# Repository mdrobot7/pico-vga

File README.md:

# Reqirements
This code was developed on Windows 11 using the Raspberry Pi Pico official C++ SDK and Visual Studio Code. It is intended to work in that environment, and no guarantees are made that it will build cleanly with no extra configuration on Linux or MacOS. However, the compiled `.uf2` file will work regardless of the OS used.

## Software Dependencies
- Raspberry Pi Pico C++ SDK, and its dependencies (see official setup instructions)
- CMake
- Visual Studio Code
- Python 3.10+
- OpenCV-Python 4.6.0+
- Numpy

## Hardware Requirements
- A Raspberry Pi Pico, obviously!
- A monitor with VGA input
- A breadboard, or a piece of protoboard/perfboard if doing a complete assembly

Since VGA is a true analog signal, it is not enough to cut up a sacrificial cable and tie it onto the Pico's pins. Some extra hardware is required to make color work, which is why a breadboard is highly recommended.

# Configuration
You **must** clone this repository ALONGSIDE the Pi Pico SDK, otherwise it WILL NOT BUILD! The file tree must look like this:

/
- pico-sdk/
- pico-vga/

### Alternative Configuration Instructions
If you absolutely cannot clone it alongside the SDK, then edit ```CMakeLists.txt``` lines 8 and 9 to match the path to those files within the SDK.

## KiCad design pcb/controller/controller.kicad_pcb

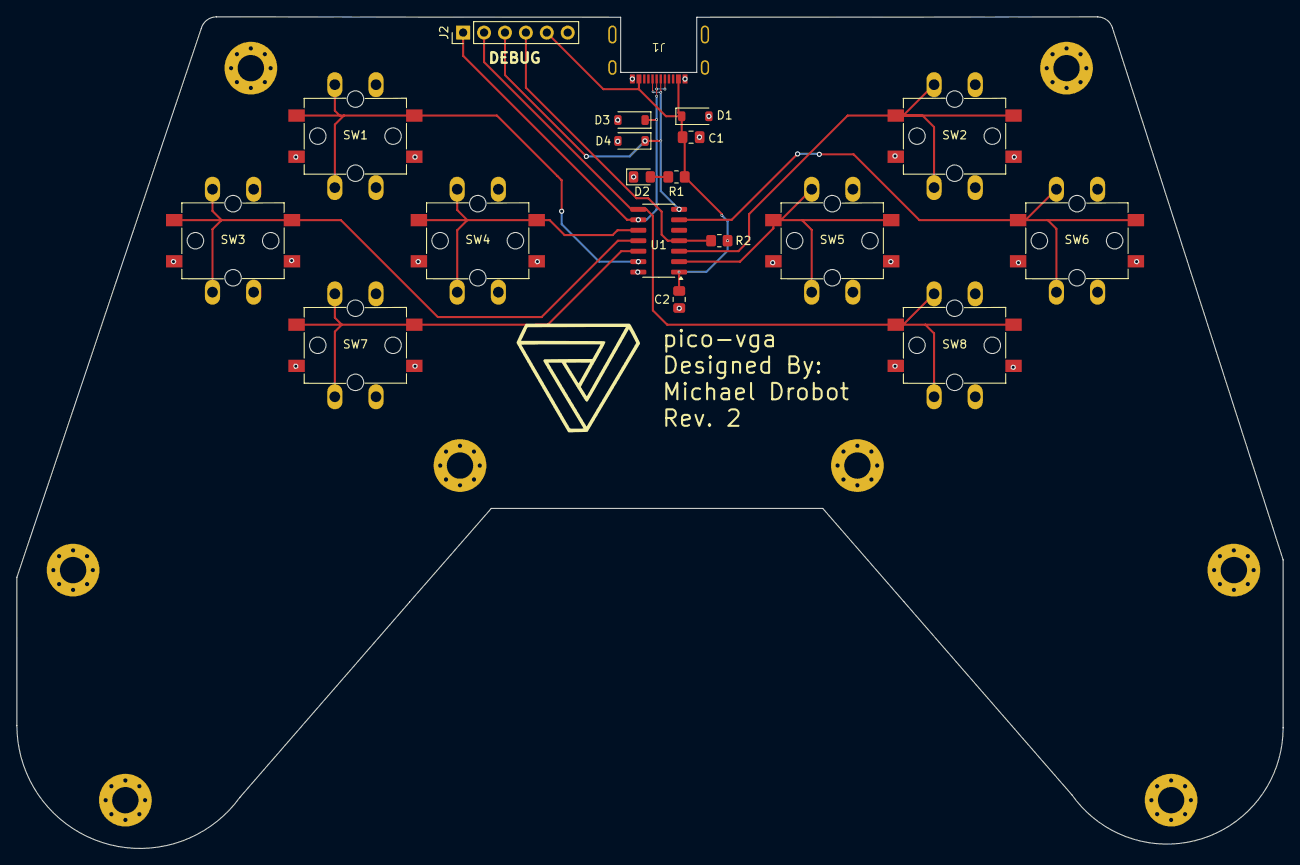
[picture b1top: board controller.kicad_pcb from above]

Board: 2 copper layers, 153.8 x 101.0 mm, 19 parts (0 on the bottom side), 14 nets.

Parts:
C1: 10u; C_0805_2012Metric_Pad1.18x1.45mm_HandSolder
C2: 100n; C_0805_2012Metric_Pad1.18x1.45mm_HandSolder
D1, D3, D4: 3.6V; D_SOD-123
D2: LED; LED_0805_2012Metric_Pad1.15x1.40mm_HandSolder
J1: USB_C_Receptacle_USB2.0_16P; USB_C_Receptacle_Molex_2169900003
J2: Conn_01x06_Pin; PinHeader_1x06_P2.54mm_Vertical
R1: 4.7K; R_0805_2012Metric_Pad1.20x1.40mm_HandSolder
R2: 4.7k; R_0805_2012Metric_Pad1.20x1.40mm_HandSolder
SW1, SW2, SW3, SW4, SW5, SW6, SW7, SW8: SW_Push; SW_Push_1P1T_12MM_SMD_AND_THT
U1: ATtiny24A-SS; SOIC-14_3.9x8.7mm_P1.27mm

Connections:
+3V3: C1.2, C2.1, D1.1 (K), J1.A4 (VBUS), J1.B4 (VBUS), J2.5, R1.1, R2.2, U1.1 (VCC)
/BTN_A: J2.2, SW8.1, U1.8 (PA5)
/BTN_B: SW6.1, U1.6 (PA7)
/BTN_DOWN: SW7.1, U1.12 (PA1)
/BTN_LEFT: SW3.1, U1.11 (PA2)
/BTN_RIGHT: SW4.1, U1.10 (PA3)
/BTN_UP: SW1.1, U1.13 (AREF/PA0)
/BTN_X: SW5.1, U1.2 (XTAL1/PB0)
/BTN_Y: SW2.1, U1.3 (XTAL2/PB1)
/MOSI: D4.1 (K), J1.A6 (D+), J1.B6 (D+), J2.3, U1.7 (PA6)
/RST: J2.4, R2.1, U1.4 (~RESET/PB3)
/SCK: D3.1 (K), J1.A7 (D-), J1.B7 (D-), J2.1, U1.9 (PA4)
GND: C1.1, C2.2, D1.2 (A), D2.1 (K), D3.2 (A), D4.2 (A), J1.A1 (GND), J1.B1 (GND), J1.S1 (SHIELD), J2.6, SW1.2, SW2.2, SW3.2, SW4.2, SW5.2, SW6.2, SW7.2, SW8.2, U1.14 (GND)
unnamed: D2.2 (A), R1.2

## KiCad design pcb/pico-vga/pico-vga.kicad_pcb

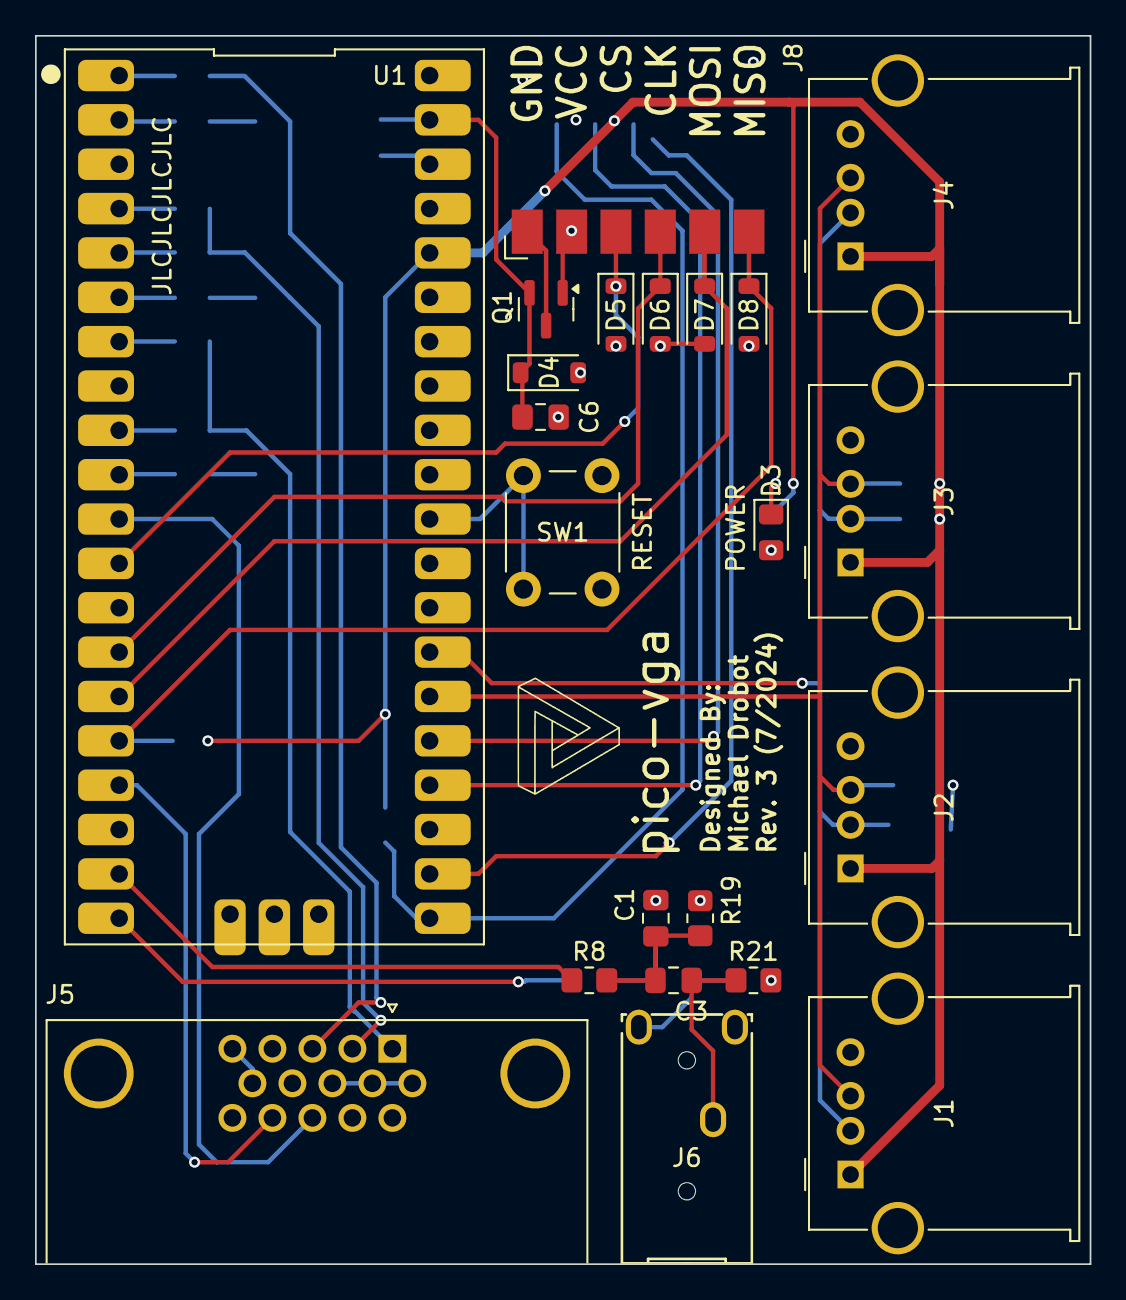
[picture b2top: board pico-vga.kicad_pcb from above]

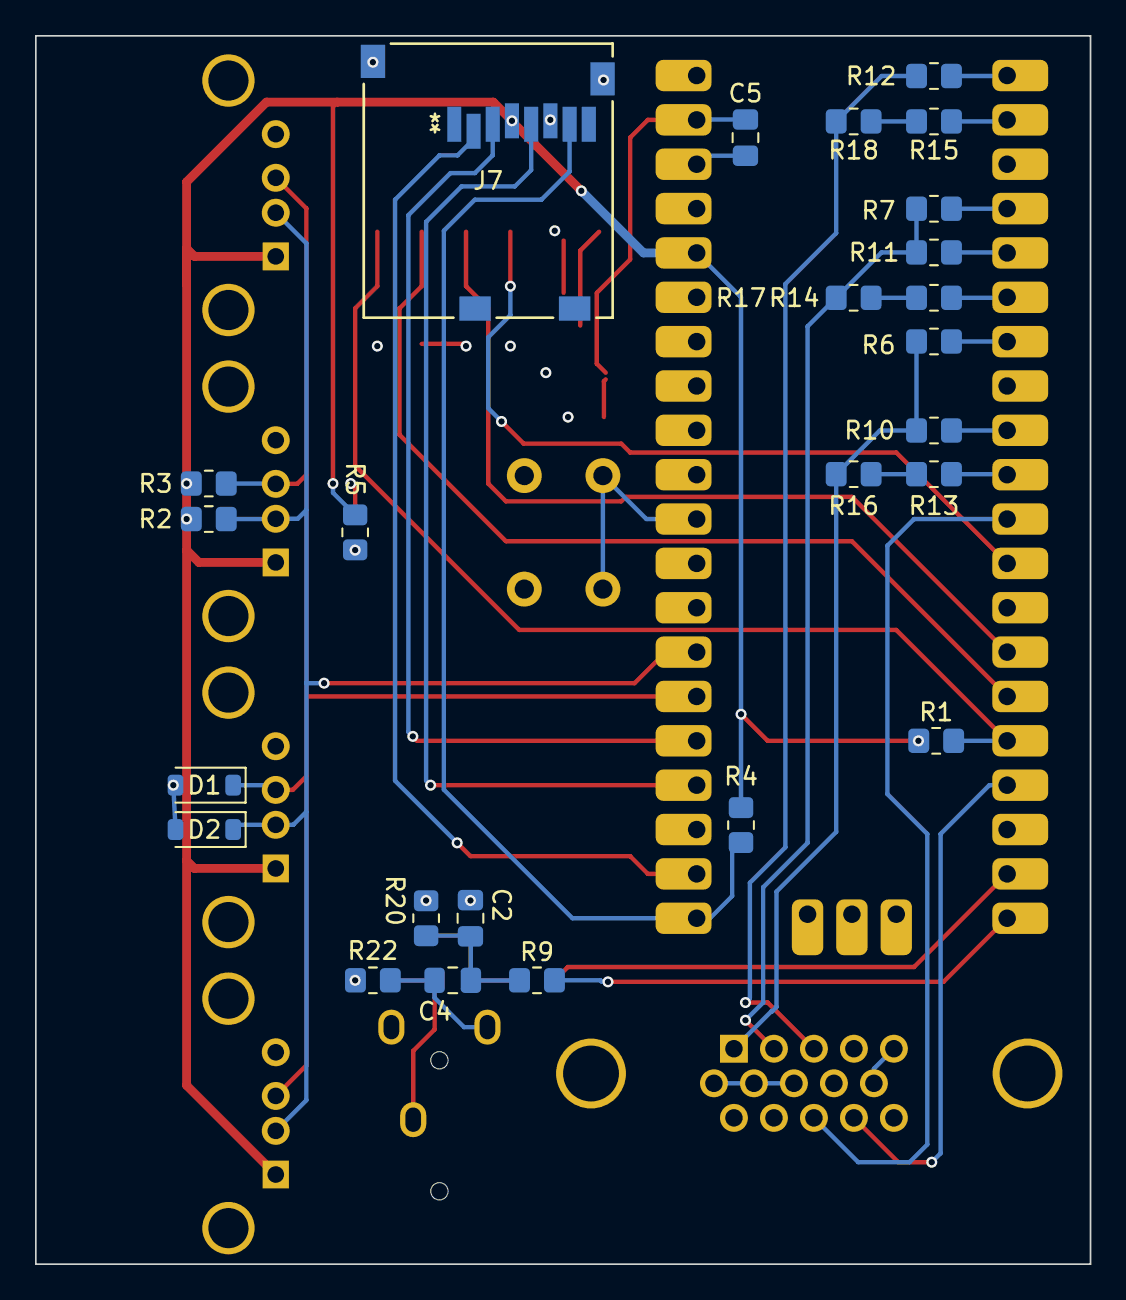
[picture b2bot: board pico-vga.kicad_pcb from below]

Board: 4 copper layers, 60.4 x 70.3 mm, 47 parts (25 on the bottom side), 38 nets.

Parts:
C1, C2, C5: 100n; C_0805_2012Metric_Pad1.18x1.45mm_HandSolder
C3, C4: 47u; C_0805_2012Metric_Pad1.18x1.45mm_HandSolder
C6: 10u; C_0805_2012Metric_Pad1.18x1.45mm_HandSolder
D1, D2, D5, D6, D7, D8: 3.6V; D_SOD-123
D3: LED; LED_0805_2012Metric_Pad1.15x1.40mm_HandSolder
D4: 5.1V; D_SOD-123
J1, J2, J3, J4: USB_A; USB_A_Molex_67643_Horizontal
J5: DB15_Female_HighDensity; DSUB-15-HD_Female_Horizontal_P2.29x1.98mm_EdgePinOffset8.35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
J6: AudioJack3; STX-3000_KYC
J7: Micro_SD_Card_Det; MEM2061-01-188-00-A_GCT
J8: Conn_01x06_Pin; PinHeader_1x06_P2.54mm_Horizontal_SMD
Q1: DMP3099L-7; SOT-23
R1, R2, R3, R4: 4.7K; R_0805_2012Metric_Pad1.20x1.40mm_HandSolder
R5, R12: 1K; R_0805_2012Metric_Pad1.20x1.40mm_HandSolder
R6, R7: 2.2K; R_0805_2012Metric_Pad1.20x1.40mm_HandSolder
R8, R9: 220; R_0805_2012Metric_Pad1.20x1.40mm_HandSolder
R10, R11: 1.2K; R_0805_2012Metric_Pad1.20x1.40mm_HandSolder
R13, R14: 470; R_0805_2012Metric_Pad1.20x1.40mm_HandSolder
R15: 390; R_0805_2012Metric_Pad1.20x1.40mm_HandSolder
R16, R17: 33; R_0805_2012Metric_Pad1.20x1.40mm_HandSolder
R18: 47; R_0805_2012Metric_Pad1.20x1.40mm_HandSolder
R19, R20: 100; R_0805_2012Metric_Pad1.20x1.40mm_HandSolder
R21, R22: 1.8K; R_0805_2012Metric_Pad1.20x1.40mm_HandSolder
SW1: SW_Push; SW_PUSH_6mm_H4.3mm
U1: Raspberry_Pi_Pico

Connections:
+3V3: J1.1 (VBUS), J2.1 (VBUS), J3.1 (VBUS), J4.1 (VBUS), J7.4 (VDD), R1.1, R2.1, R3.2, R4.1, R5.1, U1.36 (3V3(OUT))
+5V: C5.1, C6.2, D4.1 (K), Q1.2 (S), U1.39 (VSYS)
/AUDIO_L: R8.1, U1.19 (GP14)
/AUDIO_R: R9.1, U1.20 (GP15)
/BLUE_1: R15.1, U1.2 (GP1)
/BLUE_2: R12.1, U1.1 (GP0)
/CONTROLLER_SCL: D2.1 (K), J1.2 (D-), J2.2 (D-), J3.2 (D-), J4.2 (D-), R2.2, U1.27 (GP21)
/CONTROLLER_SDA: D1.1 (K), J1.3 (D+), J2.3 (D+), J3.3 (D+), J4.3 (D+), R3.1, U1.26 (GP20)
/GREEN_1: R14.1, U1.6 (GP4)
/GREEN_2: R11.1, U1.5 (GP3)
/GREEN_3: R7.1, U1.4 (GP2)
/HSYNC: J5.13, U1.11 (GP8)
/PERIPHERAL_CLK: D6.1 (K), J8.4, U1.14 (GP10)
/PERIPHERAL_CS: D5.1 (K), J8.3, U1.12 (GP9)
/PERIPHERAL_MISO: D8.1 (K), J8.6, R1.2, U1.16 (GP12)
/PERIPHERAL_MOSI: D7.1 (K), J8.5, U1.15 (GP11)
/RED_1: R13.1, U1.10 (GP7)
/RED_2: R10.1, U1.9 (GP6)
/RED_3: R6.1, U1.7 (GP5)
/SD_CLK: J7.5 (CLK), U1.24 (GP18)
/SD_CS: J7.2 (DAT3/CD), U1.22 (GP17)
/SD_MISO: J7.7 (DAT0), R4.2, U1.21 (GP16)
/SD_MOSI: J7.3 (CMD), U1.25 (GP19)
/VSYNC: J5.14, U1.17 (GP13)
GND: C1.2, C2.2, C5.2, C6.1, D1.2 (A), D2.2 (A), D3.1 (K), D4.2 (A), D5.2 (A), D6.2 (A), D7.2 (A), D8.2 (A), J1.4 (GND), J1.5 (Shield), J2.4 (GND), J2.5 (Shield), J3.4 (GND), J3.5 (Shield), J4.4 (GND), J4.5 (Shield), J5.5, J5.6, J5.7, J5.8, J5.10, J6.S, J7.6 (VSS), J7.11 (SHIELD), J8.2, Q1.1 (G), R19.2, R20.2, R21.2, R22.2, SW1.2, U1.3 (GND), U1.8 (GND), U1.13 (GND), U1.18 (GND), U1.23 (GND), U1.28 (GND), U1.33 (GND), U1.38 (GND)
unnamed: C1.1, C3.1, R8.2, R19.1
unnamed: C2.1, C4.1, R9.2, R20.1
unnamed: C3.2, J6.T, R21.1
unnamed: C4.2, J6.R, R22.1
unnamed: D3.2 (A), R5.2
unnamed: J5.1, R6.2, R10.2, R16.2
unnamed: J5.2, R7.2, R11.2, R17.2
unnamed: J5.3, R12.2, R18.2
unnamed: J8.1, Q1.3 (D)
unnamed: R13.2, R16.1
unnamed: R14.2, R17.1
unnamed: R15.2, R18.1
unnamed: SW1.1, U1.30 (RUN)

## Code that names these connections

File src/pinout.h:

#ifndef __PV_PINOUT_H
#define __PV_PINOUT_H

/*
        PINOUT (V1 + Janks)
GPIO0 - Color LSB (BLUE 2)
GPIO 1-6 - Color
GPIO7 - Color MSB (RED 1)
GPIO8 - HSync
GPIO9 - VSync (janked to GPIO10)

GPIO16 - SD Card MISO (RX)
GPIO19 - SD Card MOSI (TX)
GPIO18 - SD Card CLK
GPIO17 - SD Card Chip Select

GPIO27 - Audio L
GPIO28 - Audio R
*/

/*
        PINOUT (V3)
GPIO0  - Color LSB (BLUE 2)
GPIO 1-6 - Color
GPIO7  - Color MSB (RED 1)
GPIO8  - HSync (PWM 4A)
GPIO13 - VSync (PWM 6B)

GPIO14 - Audio L (PWM 7A)
GPIO15 - Audio R (PWM 7B)

GPIO12 - Peripheral Mode MISO (RX) (SPI1)
GPIO11 - Peripheral Mode MOSI (TX)
GPIO10 - Peripheral Mode CLK
GPIO9  - Peripheral Mode Chip Select

GPIO16 - SD Card MISO (RX) (SPI0)
GPIO19 - SD Card MOSI (TX)
GPIO18 - SD Card CLK
GPIO17 - SD Card Chip Select

GPIO20 - Controller SDA (I2C0)
GPIO21 - Controller SCL
*/

#define COLOR_LSB_PIN   0
#define HSYNC_PIN       8
#define HSYNC_PWM_SLICE (HSYNC_PIN / 2) % 8
#define HSYNC_PWM_CHAN  (HSYNC_PIN % 2)
#define VSYNC_PIN       10
#define VSYNC_PWM_SLICE (VSYNC_PIN / 2) % 8
#define VSYNC_PWM_CHAN  (VSYNC_PIN % 2)

#define AUDIO_L_PIN       27
#define AUDIO_L_PWM_SLICE (AUDIO_L_PIN / 2) % 8
#define AUDIO_L_PWM_CHAN  (AUDIO_L_PIN % 2)
#define AUDIO_R_PIN       28
#define AUDIO_R_PWM_SLICE (AUDIO_R_PIN / 2) % 8
#define AUDIO_R_PWM_CHAN  (AUDIO_R_PIN % 2)

#define SD_MISO_PIN 16
#define SD_MOSI_PIN 19
#define SD_CLK_PIN  18
#define SD_CS_PIN   17

#define PERIPHERAL_MISO_PIN 16
#define PERIPHERAL_MOSI_PIN 19
#define PERIPHERAL_CLK_PIN  18
#define PERIPHERAL_CS_PIN   17

#define CONTROLLER_SDA_PIN 20
#define CONTROLLER_SCL_PIN 21
#define CONTROLLER_I2C     i2c0

#endif

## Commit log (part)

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2022-09-06 initial commit with offline work
2022-09-06 fixed gitignore
2022-09-06 sprites, fixes for required global variables
2022-09-08 file organization
2022-09-09 PIO updates
    updated all pio files to actually be accurate to the vga signal spec, adjusted timings, and reordered some stuff. also added in presets for pins and pre-clears for interrupts.
2022-09-13 image converter finished
2022-09-25 post oscilloscope testing
    tl;dr - PIO isn't fast enough, especially if I want to scale to higher resolutions. switching over to timers in a new branch.
2022-09-26 trying some stuff
2022-10-06 clock reconfiguration, testing, NOTES
2022-10-07 800x600 update, testing complete, it WORKS!
    on an oscilloscope, still have to solder on the vga cable
2022-10-09 pico-vga PCB schematic DONE in kicad!
2022-10-10 NOW it's complete
    kicad decided to delete all of my resistor/cap values sometime before the last commit... values are back now, everything's labeled, passes ERC
2022-10-15 Pico-VGA and Controller PCBs DONE!
    Updates to pico-vga: I don't remember.... Uhhh.... I did stuff? Whatever, I like the layout, it passes DRC, it's badged, and it now has mounting holes. Updates to controller: It now exists. It also p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
2022-10-16 moved sd card slot, reset switch, power led
    when I added the mounting holes it lengthened the board, and the sd slot, power led, and reset switch were in a pretty bad place. Moved them back to the edge of the board, redid traces, and it passes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
2022-10-20 BOM update
2022-10-20 Filled in skeleton code
    Most draw methods are now done, initialization, and background management is done
2022-10-22 added auxiliary SPI and power headers to pcb
    added a header for SPI to the board, so the board can act as a peripheral for other devices, and data/commands can be sent over SPI. also added auxiliary power connector, meant to be used when the bo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
2022-10-23 replaced render queue with linked list
    this makes memory use more efficient, dynamically sizes the array which gets rid of any risk of filling it up, makes memory management better.
2022-10-29 BOM update: changed a link
2022-11-02 fixed DMA transfers, organized project
    fixed DMA so it now doesn't transfer important data during the hSync period (it will just transfer garbage and reset the transfer start address at the start of the next line).
2022-11-03 added insertion/deletion support, prototyped color convert funcs
2022-11-09 Merged testing results with main project
2022-11-20 testing issues
    These are changes from testing. I ran into a lot of problems in actually implementing single line renderer (it's not fast enough, I don't think), so I'm branching. Committing before branch.
2022-11-22 changed to single full frame buffer and 400x300
    rewrote sdk.c to render a full frame worth of buffer, rather than just lines, and drop the resolution down to 1/4 scale (400x300) instead of full res. Testing soon
2022-11-25 testing, part 2
    after more testing, I ran into an issue that I can't find any reasonable explanation for. at random intervals of a few seconds, the frame shifts either down a line or down and to the left a line/colu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
2022-12-14 more testing
    I'm gonna clean up the files, committing beforehand in case I delete something important
2022-12-15 IT WORKS!!!!!!
    FINALLY! I got a full color gradient on the screen, no shifting in any direction, no glitchiness, no stuttering... IT WORKS!
2022-12-23 Tried to implement dynamic resolution
    Tried to implement dynamic resolution with a calloc() call in the init function, but I ran into some weird issues. Problem for another day, I'm sticking this in a branch and I'll deal with it later
2022-12-24 Moved DMA IRQ callback to second core
2022-12-26 Documentation update
2023-01-01 Update docs
2023-01-03 splitting the SDK, part 1
    I'm splitting the SDK into multiple files to organize it better and make it easier to read. Running into problems, so I'm going to come back to this later
2023-01-03 Fixed building issues, finished splitting SDK
    Fixed the building issues, one header can't be included into multiple C source files without causing issues. Changed to using extern and defining the variables/arrays in one of the C sources. (thanks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
2023-01-04 finished the cp437 font
    spent all day translating the cp437 font from an image I found online to a binary bit array. that took forever.
2023-02-16 started refactoring renderer
    started splitting renderer into multiple render functions for each element. may be rewriting the renderer entirely, but I have to do some research beforehand
2023-02-20 Refactoring, started dynamic resolution
    Moved some stuff around. Most of the changes were starting dynamic resolution, where the frame buffer and all of the large arrays are dynamically allocated. Did most of it, but the DMA interrupt stil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
2023-02-20 More work on dynamic resolution, added deInits for all modules
    added some features to dynamic resolution, reconfiguring some of the PIO stuff so that the color offset can be set at runtime. Also made deinitializers for all lib modules -- all can be initialized a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
2023-02-28 commit before switching devices
2023-03-16 Rewrote drawing functions to use new memory management system
    Switched to doing memory management myself instead of using malloc() last commit, this is the actual implementation of that. Rewrote RenderQueueItems to be better for 3D and more flexible for 2D, at 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
2023-04-01 Started rewriting renderer
    Started rewriting renderer to be faster and use better algorithms, along with adding more features. It's a mess right now. Also wrote a garbage collector for the new memory management system
2023-04-11 Started planning audio
    Planned out how to make a basic RTTTL based audio system, but that would be literally worse than the NES. I'm rethinking it, I might implement RTTTL as a placeholder but I need to find a prof that kn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
2023-04-22 Renderer update part 1
    Refactoring the renderer to be in its own "submodule". Also moving low-level functions (bresenham stuff) to other subfiles to declutter. In the process of adding documentation too
2023-05-03 Recalibrated color signal for dorm monitor
2023-05-05 Working PWM sync lines for 800x600
    Still haven't tested with color, and this is bench testing on a scope. Will test later tonight
2023-05-05 First attempt
    My guess is this won't work, I think the sync signals will look fine but once you integrate color it will break because of the frame full height being an odd number. We'll see
2023-05-05 Forgot a few lines, finished bench testing
    Will test with color on a monitor later, my guess is I'll run into a few issues since the true height of the frame is 525 (an odd number) and I don't think my code handles that well
2023-05-11 Started audio
    After some research, decent quality WAV audio is actually incredibly simple -- IF you have a good source clock (fast enough and a multiple of your sample rate). I don't, so we'll see how it goes
2023-05-12 Fixed sync issues, finished testing
    Did some research -- just using a 25MHz pixel clock with 640x480 doesn't work, you have to do a bit of extra modification. You need to either shorten the width or height. I followed the timings from 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
2023-05-23 PWM sync signals update, "merging" pwm-sync-x branches
    After extensive testing and validation, the pwm-based sync stuff is finally ready. I "merged" it into the main code (the testing branches are based on such an old version of my code that I couldn't m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
2023-05-24 cleanup part 1 of many
    Fixed includes, so now the includes relevant to each file are at the top of each file rather than some being in lib-internal.h. Also removed old unused includes
2023-05-27 SDK-ification complete
    I decided to remove all direct register writes and replace them with calls to the pico sdk. It makes the code a bit more readable for other people using the pico who may not be used to direct writes.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
2023-05-29 PCB update and BOM
    Remade the BOM so now you can just export to csv and throw it into digikey, makes it a lot easier. In making the BOM I realized some of my old parts were super expensive, so I redid some components
2023-05-31 Forgot I2C pullup resistors, updated Sch, PCB, and BOM
2023-06-02 Controller updates
    I've had random brainstorming sessions the past few days on how to handle this, and I think I've come up with a decent method. It's basically CPU-less, runs entirely off the DMA. There is one channel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
2023-06-16 Update to new pico windows installer, new sdk
2024-07-30 Add JLC tag to pico-vga PCB
2024-08-05 File restructuring, build system fixes
    - I don't know what on earth I was thinking the first time I did this.....
    Now at least the library is in a coherent file structure, similar to other C
    library standards. Much cleaner.
    - A /lib folder will be added for external/third party libraries should I need it
2024-09-02 Moving stuff around, general restructuring
    - Modularizing everything. Each "module" of the library will have its own init/deinit functions, prefixing, and header.
    - Removing old unnecessary stuff after the render queue change
    - Shelving peripheral mode and SD for now. Removing their source files to simplify the file tree
2024-09-03 Library restructuring part ????
    - Make each "module" into its own directory to clean up the file tree
    - Still running off of one master cmakelists, adding more seems redundant
2024-09-03 Add clang-format
    - Borrowed Gregory's clang-format here, I'll probably end up modifying it eventually since there are certain bits I don't like.
    - Format the whole workspace
2024-09-03 Update draw-2d and vga header file
    - Update all draw functions to new render queue item format
    - I settled on a way to do store simple polygons in render queue items
    - Make the points */num_points section a union, use it to store type-specific data
    - This keeps the formatting pretty consistent, while keeping basic shapes like triangles
    fully accessible without following a pointer (cache miss)
    - Remove "future" features from the current version
2024-09-06 Nuke utils-internal
    - Everything inside was either out of date, macrotized, or I'll just come back to later
2024-09-07 Finally got it to compile, refactored audio module
    - Refactored audio module so it matches the file structure/naming scheme
    - Finally got the project to compile cleanly, holy crap that took forever
2024-09-07 Fix line doubling in render_pixel
2024-09-14 Controller rev 2
    - Using an attiny24 and I2C now to communicate between the mainboard and the controllers
    - Gets rid of the massive multiplexer on the mainboard, simplifies things
    - Attiny software will probably be written in arduino because I'm lazy
    - Swapped the connector for a cheaper one since we don't need all 24 pins, still using usb-c though
    - Button layout stays the same
2024-09-28 Mid-debug, nothing's working
    - The old, stable, low-level vga drivers are borked for some reason. I'm not getting a display output, and it's not recognizing the sync signals. Checking out something older to investigate
2024-09-29 SDK-ifying the dma calls
    - Testing this here because main is a dumpster fire right now. Good news, it works
2024-10-06 PWM enable and frame_read_addr bugs fixed
2024-10-06 You cannot be serious
    - 10 hours of software debug all for one compiler flag.
    - DO YOU KNOW HOW MUCH OF MY SANITY THIS COST ME
    - >:(
2024-10-06 Cleanup from testing, basic video demo
    - Should show a red filled rectangle in the middle of the screen, with a white border around the 800x600 area
2024-10-06 Getting-started demo got started, a few renderer issues
    - If you move or shrink an item at all, it leaves "ghosts" behind that don't get cleared unless you force-refresh
    - Forcing a full rerender after every small update is *really* slow, it looks like trash
    - DMA in the _fill and _rectangle_fill functions may help, but probably not by a ton
    - Not sure what to do about this, I'll deal with it when I can think
2024-10-07 Death to camel case
